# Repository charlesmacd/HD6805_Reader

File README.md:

# HD6805_Reader
(C) 2021 Charles MacDonald

WWW: http://techno-junk.org

Arduino shield used to read the internal ROM of some Hitachi HD6805 devices.

Based on the information and research of Sean Riddle (https://seanriddle.com/mc6805p2.html)

**NEW**: Check out the Dumping Log in the Wiki: https://github.com/charlesmacd/HD6805_Reader/wiki
 
## Overview

This project came about from the need to read the HD6805V1 MCU used in Sega's SP-400 printer.

## Files

```
/windows/hdread.exe
	Utilty to talk to Arduino via USB and retrieve HD6805 data
/utility 
	Utility source code
/firmware
	Arduino Uno firmware
/pcb/v1 
        Prototype shield
	Eagle schematics and layout for the first version of the shield. 
	Needs some wire links and a capacitor marked in yellow.
/pcb/v2
        Revised version of shield
	Eagle schematics and layout for the second version, fixes all the issues in v1
/pcb/gerbers
	Gerber files. These were set up using design rules for Elecrow/JLCPCB but 
	you definitely want to generate your own gerber	files for the fab you use.
/images
	Pictures of the shield
/datasheets
	Datasheets, patents, and other relevant material
```

## How to use

1. Insert the HD6805V1 device into the DIP socket with the pin 1 indicator facing toward the Arduino UNO's USB port.
2. Plug the Arduino Uno's USB cable into your PC.
3. Run the utility program: ```hdread read dump.bin```. It gives the following output

```
Status: Found port COM8.
Status: Attempting to open COM8.
Status: Waiting for Arduino to reboot.
Sending command.
Got command parameter = 06
Status: Test address wrapping.
Status: Seek first bus cycle.
Result: Found first bus cycle in 19 clocks.
Status: Seek first bus cycle.
Result: Found output sequence in 16 clocks.
Status: Seek zero bus cycle.
Result: Found address wrap in 4880 clocks.
Reading offset 0000
:
Reading offset 0F00
Checksum = 78
Status: Finished.
Normal exit.
Status: Normal exit.
Local checksum = 78
Status: Writing ROM image to file `dump.bin'.
Status: Writing decoded data to `dump.bin.log'.  
```

4. The ROM data is written to ```dump.bin```, and the raw data output for each NUM cycle is written to ```dump.bin.log```. The latter isn't necessary but can be useful for examining the reading sequence in more detail.

Note that while the entire 4K address space is dumped ROM data only corresponds to offsets 0x0080 to 0xFFF. The first 128 bytes are mapped to internal I/O, RAM, and unused areas and will not be consistent from dump to dump. The utility program blanks them out to 0xFF, but doesn't do that to the log file.

## Analyzing dumped data

You can run ```hdread check <file.bin>``` to analyze the self-check ROM data, if present. For a HD6805V1 it reports the following:

```
Self-check vectors:
* TIMER = $0FEA
* INT#  = $0FEC
* SWI   = $0FE7
* RES#  = $0F80
Customer vectors:
* TIMER = $0A46
* INT#  = $0A10
* SWI   = $07F0
* RES#  = $06E0
Self-check ROM analysis:
* Reset vector is valid.
* Internal checksum   = EA
* Calculated checksum = EA
* ROM SHA256 = 9088fee917e5a748c2f0b4f5458c1cbdabbd696291c69be6e605bae0ef779e8f
* ROM matches device type HD6805V1
```

The internal checksum is stored within the self-check ROM at address 0xFEF. It is computed by calculating the exclusive OR of all bytes from 0x080 to 0xFFF excluding 0xFEF and inverting the result. If the internal and calculated checksums don't match it's likely the ROM dump is bad and should be redumped.

The sha256sum covers addresses 0xF80 through 0xFE7. Two devices I dumped have identical programs, but it's possible other HD6805 variants have different
self-check programs. Please get in touch if you find a device with a different sha256sum.

## Board assembly and configuration

The original design had a TPS2041B to control power to the HD6805V1 in case there was any behavior worth examining that was tied to a power-up event, but in practice that isn't necessary. Thus components IC1, C1A, C1B, C2A, C2B, R8, R10, R24 and the yellow LED can be omitted.

### Board types

The V1 design was the first one I made and it works fine but needs some corrections:

* Wire links added from C0-C4 and NUM to Arduino inputs A0-A4 and A5.
* A 0.1uF capacitor across DIP socket pins 1,4.

The V2 design has these changes made and the schematic was cleaned up considerably so I'd advise building that one instead.
I haven't tested it myself but it was a minor set of changes.

### Bill of materials

| Location | Size | Type | Manufacturer P/N |
|- |- |- |- |
| C1A,C2A | 0603 | Ceramic, 0.1uF, 10V | C0603C104Z3VACTU |
 |C1B,C2B | 0603 | Ceramic, 0.01uF, 10V | 06035C103KAT2A |
| R1-R8/R11-R15/R16-R24 | 0603 | 1K ohm, 1/10W, any tolerance | CRCW06031K00FKEAC |
| R9/R10 | 0603 | 10K ohm, any tolerance | SFR03EZPF1002 |
| FLT | 3mm | Yellow LED, diffused | TLHY4400-AS12Z |
| IC1 | SOIC-8 | TPS2041B load switch | TPS2041BD |
| JP3/4/6/7 | N/A | Arduino UNO stacking headers | Adafruit P/N: 485 or Mouser P/N: 485-85 |

### Jumper configurations

See the photo for more details.

* For JP11 pins 2-3 should be shorted together so that the Arduino 5V is used for the HD6805V1 +5V input.

* For JP5 the jumper across all pins should be installed. Note on the V1 board the middle jumper (XTL) should be left open.

* For JP9-10 the jumpers should be arranged to specify 0x9D (from top to bottom is MSB to LSB, left=VCC, right=GND so jumper order is LRRLLLRL)

## Tested devices

1. ```Hitachi HD6805V1P A08```
   Dump seems good. Internal checksum is 0xEA.

2. ```Termbray 117-017 HD6805V1B65P 8A3```
   Dump seems good. Internal checksum is 0x8A. Same self-check ROM content as above.

3. ```Hitachi HD6805V1A81P 800-5 A24```

   Dump seems good. This is a variant where the self-check ROM is not present and instead contains more customer ROM code and data.
   Thus the self-check mode is not supported and only the user vector table is present.

Note that all the chips run a somewhat hot normally.
The Arduino Uno I tested with draws about 40mA idle, and with a HD6805V1 installed it draws 120mA when the clock is static.
But use caution when testing the PCB after assembly and check all voltages **before** inserting a chip and attempting to read it.

## Technical overview

The HD6805V1 is a variant of the Motorola MC6805 designed by Hitachi. Check out the datasheet for more information.

### Memory map
```
0000-0009 : Internal registers (I/O, timer)
000A-001F : Unused
0020-007F : Work RAM (96 bytes)
0080-0F7F : Customer ROM (3848 bytes)
0F80-0FEF : Self-check ROM (120 bytes)
0FF0-0FF7 : Self-check ROM vector table
```

## Operating modes
* Normal
  * Customer ROM is used
* Self-check
  * Self-test ROM is used
  * Enable by pulling TIMER pin to +9V 
* Non-user mode
  * External ROM is used
  * Enable by pulling NUM pin to +5V

## Non-user mode

In non-user mode the I/O ports are repurposed to present an external memory bus similar to the MC146805E2:

* Port A is the external data bus where opcodes are input.
* Port B is multiplexed between part of the address bus and the internal data bus.
* Port C outputs several address lines on PC[4,2:0] and a control signal, possibly R/W# on PC3.

This arrangement would allow the HD6805V1 to execute program code from an external EPROM. A slight difference between it and the MC146805E2 is how the address bus is arranged:

* PB[7:0] => {A9, A8, A5, A5, A6, A1, A7, A0}
* PC[4,2:0] => {A11, A3, A2, A10}

What's missing is a signal used to demultiplex port B. Hitachi's US patent 5,179,694 describes a function for the HD6301V microcontroller where the E clock (a synchronization signal that runs at 1/4th of the oscillator clock) isn't normally accessible but can be output in some conditions. It follows with a brief note that the HD6805 NUM pin performs a similar function when it is pulled high, outputting the sync signal for device testing purposes.

Tests on the HD6805V1 confirms this; in non-user mode the NUM pin will output a clock signal at 1/4th of the rate presented on the EXTAL pin. Conceptually this seems to map closest to the MC146805E2's DS signal. This can be used to demultiplex port B.

## Device configuration in NUM mode for dumping internal ROM

For dumping ROM data I configured the pins as follows on the Arduino shield:

* RES# : Pulled high via 1K ohm resistor, can be driven low to reset the device and restart the output stream of data.
* INT# : Pulled high via 1K ohm resistor, unused
* EXTAL : Driven by Arduino to clock the HD6805V1
* XTAL : I've left it floating with good results, but it should probably be grounded.
* NUM : Pulled high via 1K ohm resistor, in NUM mode it becomes a sync output used to demultiplex port B
* TIMER : Pulled high via 1K ohm resistor
* PB[7:0],PC[2:0],NUM : Input to Arduino for logging
* PA[7:0] : Connected to eight jumpers to specify an opcode (in this case 0x9D for NOP)
* PD[7:0] : Unused, pulled high via 1K ohm resistor network. The pull-ups may not be necessary.
* PC[7:3] : Unused

## Exploiting non-user mode

The most useful side effect of non-user mode is that the internal data bus multiplexed on port B outputs whatever internal memory location the program counter is currently addressing, allowing the entirety of the HD6805V1 address space to be read out. To control this process to dump ROM data a simple 1-byte instruction like NOP or RSP can have their opcode driven on to port A and the HD6805 will continuously execute it, output data from the current internal address, and increment the program counter by one. This process can continue indefinitely until all ROM data has been read.

## Reset timing

* Clock cycle 1 : NUM low, port B,C output address 0xFFE.
* Clock cycle 2 : NUM high, port B outputs data from internal ROM address 0xFFE. This is the reset vector LSB.
* Clock cycle 3 : NUM low, port B,C output address 0xFFF.
* Clock cycle 4 : NUM high, port B outputs data from internal ROM address 0xFFF. This is the reset vector MSB.
* Clock cycle 5 : NUM low, port B,C output address 0x000.
* Clock cycle 6 : NUM high, port B outputs 0xFF.
* Clock cycle 7 : NUM low, port B,C output address 0xD9D.
* Clock cycle 8 : NUM high, port B outputs data from internal ROM address 0xD9D.

Before this sequence starts there can be 18 to 20 clocks needed for the HD6805V1 to come out of the reset state.

Since we're gating NOP (0x9D) on to port A, the reset vector read is 0xD9D.

## NOP execution timing

* Clock cycle 1 : NUM low, Port B outputs address.
* Clock cycle 2 : NUM high, port B outputs internal data bus.
* Clock cycle 3 : NUM low, Port B outputs address.
* Clock cycle 4 : NUM high, port B outputs internal data bus. At the next clock edge the program counter increments.

As long as NOP or a similar type of opcode is presented this sequence repeats indefinitely.

Here cycles 3,4 present the same data and address as cycles 1,2. When reading ROM the data will be consistent, but when reading first 128 bytes assigned to
I/O, RAM, and unused locations the data can differ.

## Dumping ROM data

As the Arduino shield always outputs 0x9D on to port D, the reset vector is 0xD9D and internal data starts getting fetched from that address.
A more complex device might want to dynamically drive port A to define a reset vector like 0x000 or 0x080, it's simple enough to clock the device 
until the address bus increments from 0xD9D to 0xFFF and then wraps to 0x000. At this point the entire 4K internal address space can be read out.

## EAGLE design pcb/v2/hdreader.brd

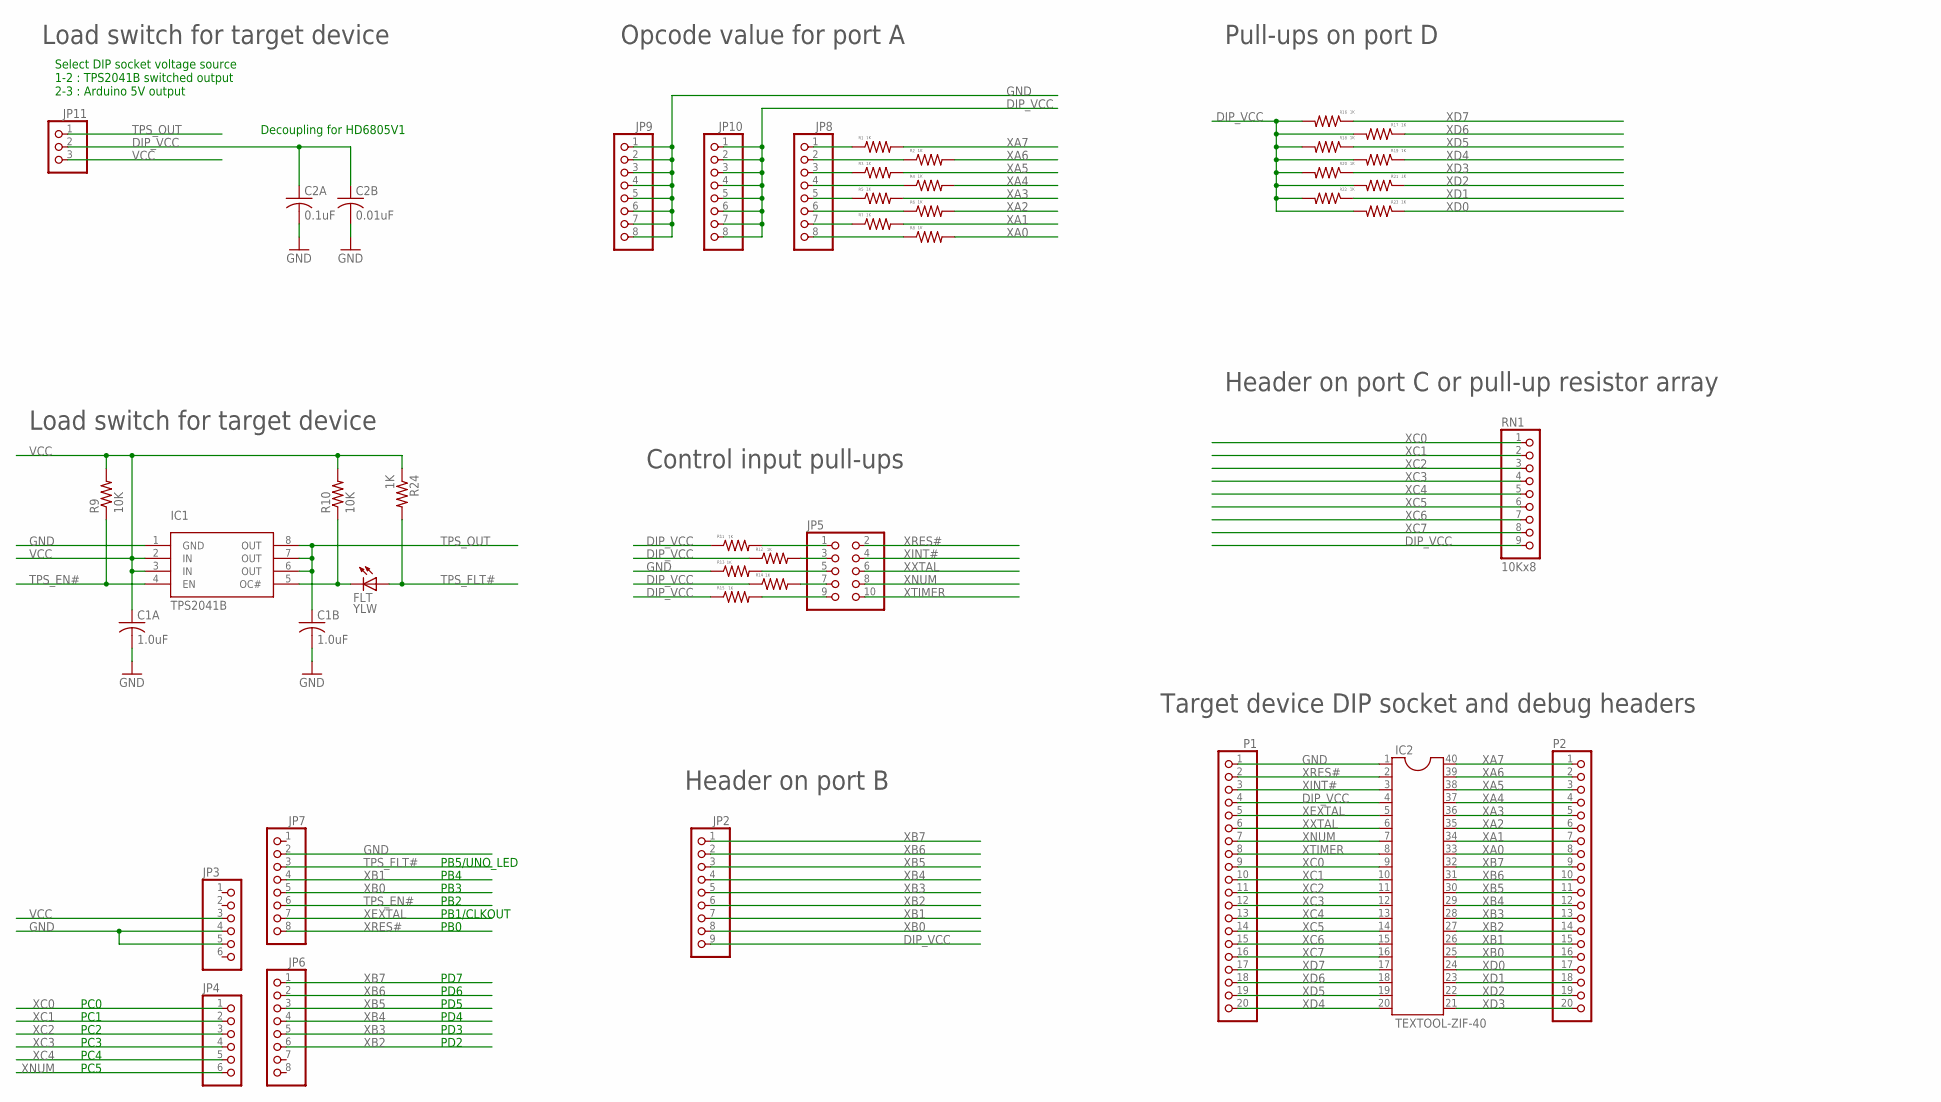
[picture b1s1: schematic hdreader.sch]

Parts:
C1A, C1B: 1.0uF; C0603
C2A: 0.1uF; C0603
C2B: 0.01uF; C0603
FLT: YLW; LED5MM
IC1: TPS2041B; SOIC8
IC2: TEXTOOL-ZIF-40; TEXTOOL-DIP-40
JP2: PINHD-1X9; 1X09
JP3, JP4: PINHD-1X6; 1X06
JP5: PINHD-2X5; 2X05
JP6, JP7, JP8, JP9, JP10: PINHD-1X8; 1X08
JP11: PINHD-1X3; 1X03
P1, P2: PINHD-1X20; 1X20
R1, R2, R3, R4, R5, R6, R7, R8, R11, R12, R13, R14, R15, R16, R17, R18, R19, R20, R21, R22, R23, R24: 1K; R0603
R9, R10: 10K; R0603
RN1: 10Kx8; 1X09

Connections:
DIP_VCC: C2A.1, C2B.1, IC2.4, JP2.9, JP10.1, JP10.2, JP10.3, JP10.4, JP10.5, JP10.6, JP10.7, JP10.8, JP11.2, P1.4, R11.1, R12.1, R14.1, R15.1, R16.2, R17.2, R18.2, R19.2, R20.2, R21.2, R22.2, R23.2, RN1.9
GND: C1A.2, C1B.2, C2A.2, C2B.2, IC1.1 (GND), IC2.1, JP3.4, JP3.5, JP7.2, JP9.1, JP9.2, JP9.3, JP9.4, JP9.5, JP9.6, JP9.7, JP9.8, P1.1, R13.1
unnamed: FLT.A, R24.2
unnamed: JP5.1, R11.2
unnamed: JP5.3, R12.2
unnamed: JP5.5, R13.2
unnamed: JP5.7, R14.2
unnamed: JP5.9, R15.2
TPS_EN#: IC1.4 (EN), JP7.6, R9.1
TPS_FLT#: FLT.K (C), IC1.5 (OC#), JP7.3, R10.1
TPS_OUT: C1B.1, IC1.6 (OUT), IC1.7 (OUT), IC1.8 (OUT), JP11.1
VCC: C1A.1, IC1.2 (IN), IC1.3 (IN), JP3.3, JP11.3, R9.2, R10.2, R24.1
XA0: IC2.33, P2.8, R8.2
XA1: IC2.34, P2.7, R7.2
XA2: IC2.35, P2.6, R6.2
XA3: IC2.36, P2.5, R5.2
XA4: IC2.37, P2.4, R4.2
XA5: IC2.38, P2.3, R3.2
XA6: IC2.39, P2.2, R2.2
XA7: IC2.40, P2.1, R1.2
XAP0: JP8.8, R8.1
XAP1: JP8.7, R7.1
XAP2: JP8.6, R6.1
XAP3: JP8.5, R5.1
XAP4: JP8.4, R4.1
XAP5: JP8.3, R3.1
XAP6: JP8.2, R2.1
XAP7: JP8.1, R1.1
XB0: IC2.25, JP2.8, JP7.5, P2.16
XB1: IC2.26, JP2.7, JP7.4, P2.15
XB2: IC2.27, JP2.6, JP6.6, P2.14
XB3: IC2.28, JP2.5, JP6.5, P2.13
XB4: IC2.29, JP2.4, JP6.4, P2.12
XB5: IC2.30, JP2.3, JP6.3, P2.11
XB6: IC2.31, JP2.2, JP6.2, P2.10
XB7: IC2.32, JP2.1, JP6.1, P2.9
XC0: IC2.9, JP4.1, P1.9, RN1.1
XC1: IC2.10, JP4.2, P1.10, RN1.2
XC2: IC2.11, JP4.3, P1.11, RN1.3
XC3: IC2.12, JP4.4, P1.12, RN1.4
XC4: IC2.13, JP4.5, P1.13, RN1.5
XC5: IC2.14, P1.14, RN1.6
XC6: IC2.15, P1.15, RN1.7
XC7: IC2.16, P1.16, RN1.8
XD0: IC2.24, P2.17, R23.1
XD1: IC2.23, P2.18, R22.1
XD2: IC2.22, P2.19, R21.1
XD3: IC2.21, P2.20, R20.1
XD4: IC2.20, P1.20, R19.1
XD5: IC2.19, P1.19, R18.1
XD6: IC2.18, P1.18, R17.1
XD7: IC2.17, P1.17, R16.1
XEXTAL: IC2.5, JP7.7, P1.5
XINT#: IC2.3, JP5.4, P1.3
XNUM: IC2.7, JP4.6, JP5.8, P1.7
XRES#: IC2.2, JP5.2, JP7.8, P1.2
XTIMER: IC2.8, JP5.10, P1.8
XXTAL: IC2.6, JP5.6, P1.6

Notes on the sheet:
PB0
PB1/CLKOUT
PB2
PB3
PB4
PB5/UNO_LED
PD2
PD3
PD4
PD5
PD6
PD7
Select DIP socket voltage source 1-2 : TPS2041B switched output 2-3 : Arduino 5V output
Decoupling for HD6805V1
PC0
PC1
PC2
PC3
PC4
PC5
Load switch for target device
Opcode value for port A
Control input pull-ups
Header on port C or pull-up resistor array
Header on port B
Target device DIP socket and debug headers
Pull-ups on port D

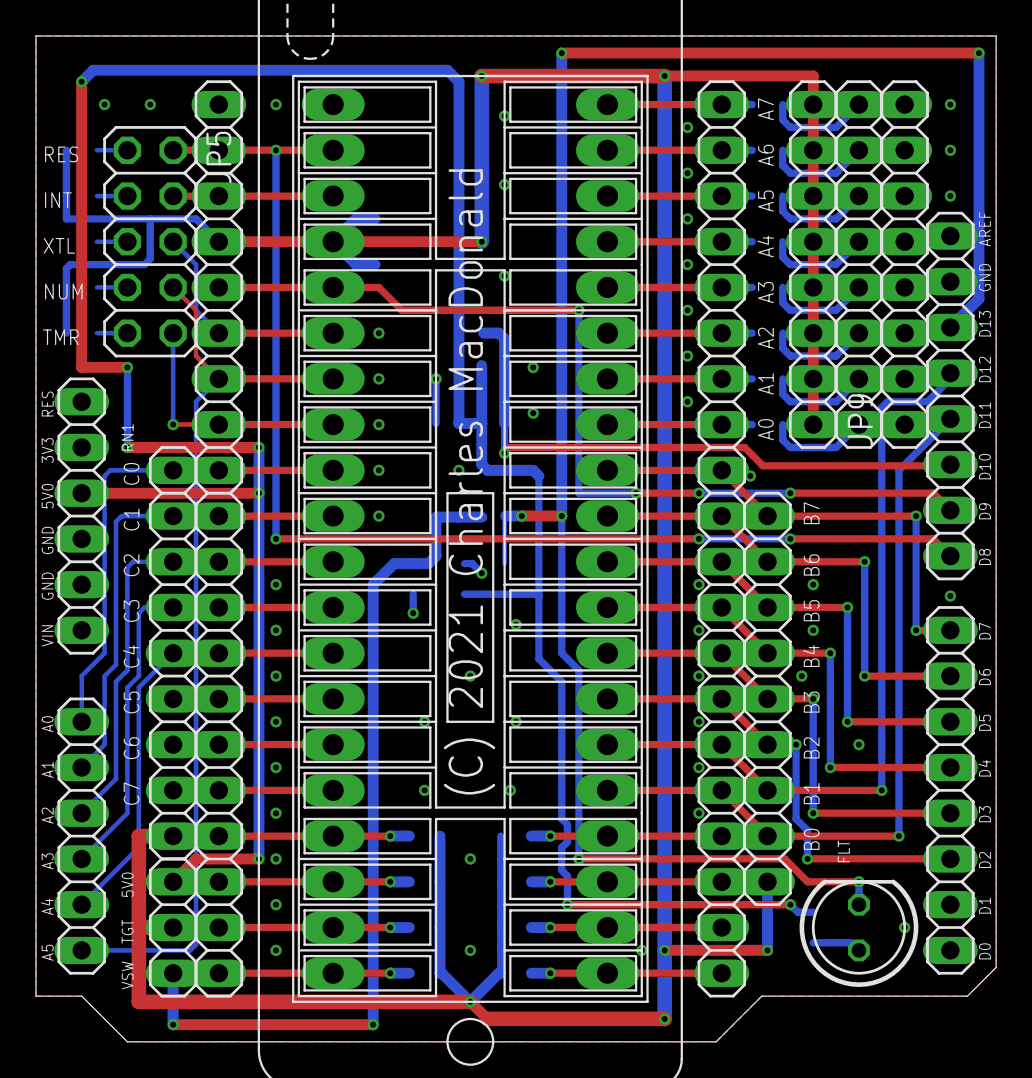
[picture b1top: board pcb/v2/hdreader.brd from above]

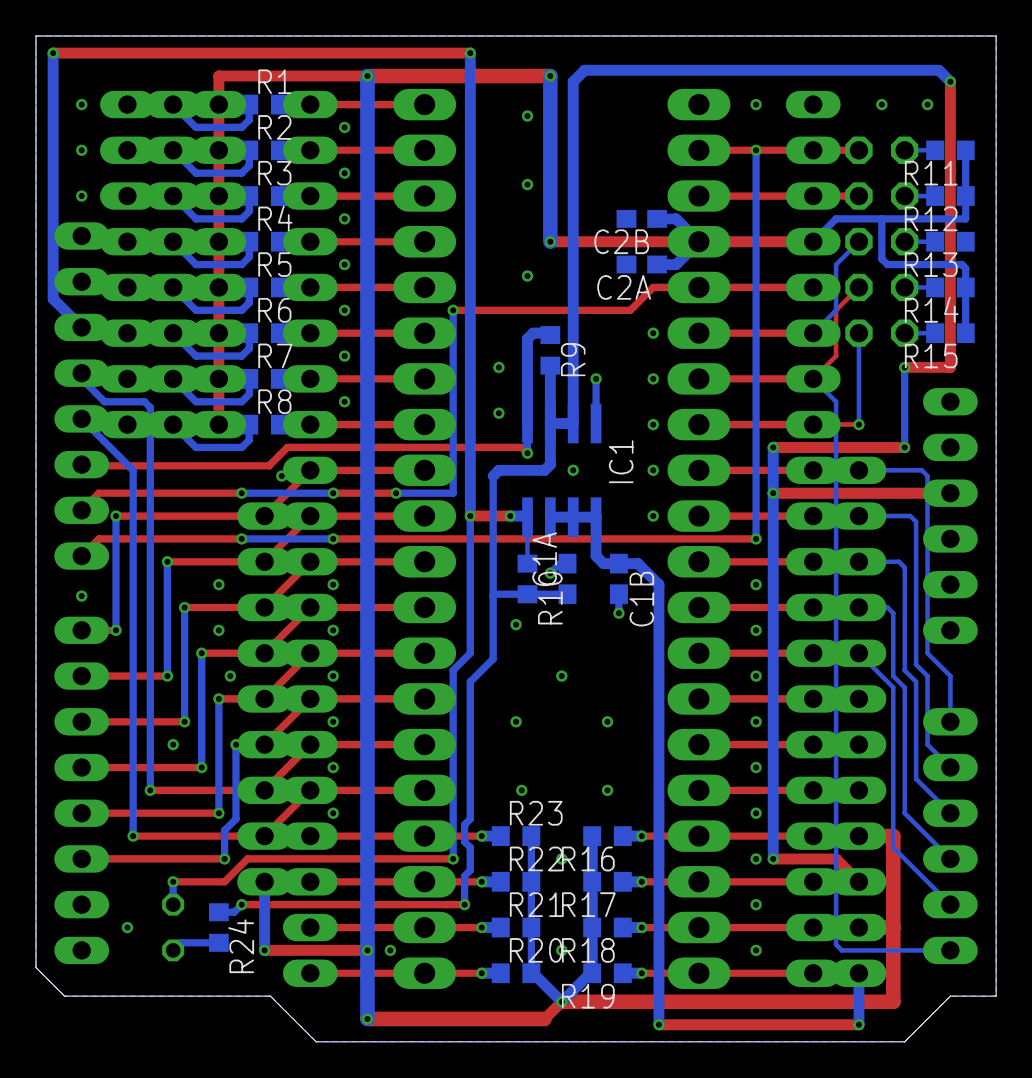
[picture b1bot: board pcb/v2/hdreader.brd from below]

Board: 2 copper layers, 53.3 x 55.9 mm, 44 parts (29 on the bottom side), 58 nets.

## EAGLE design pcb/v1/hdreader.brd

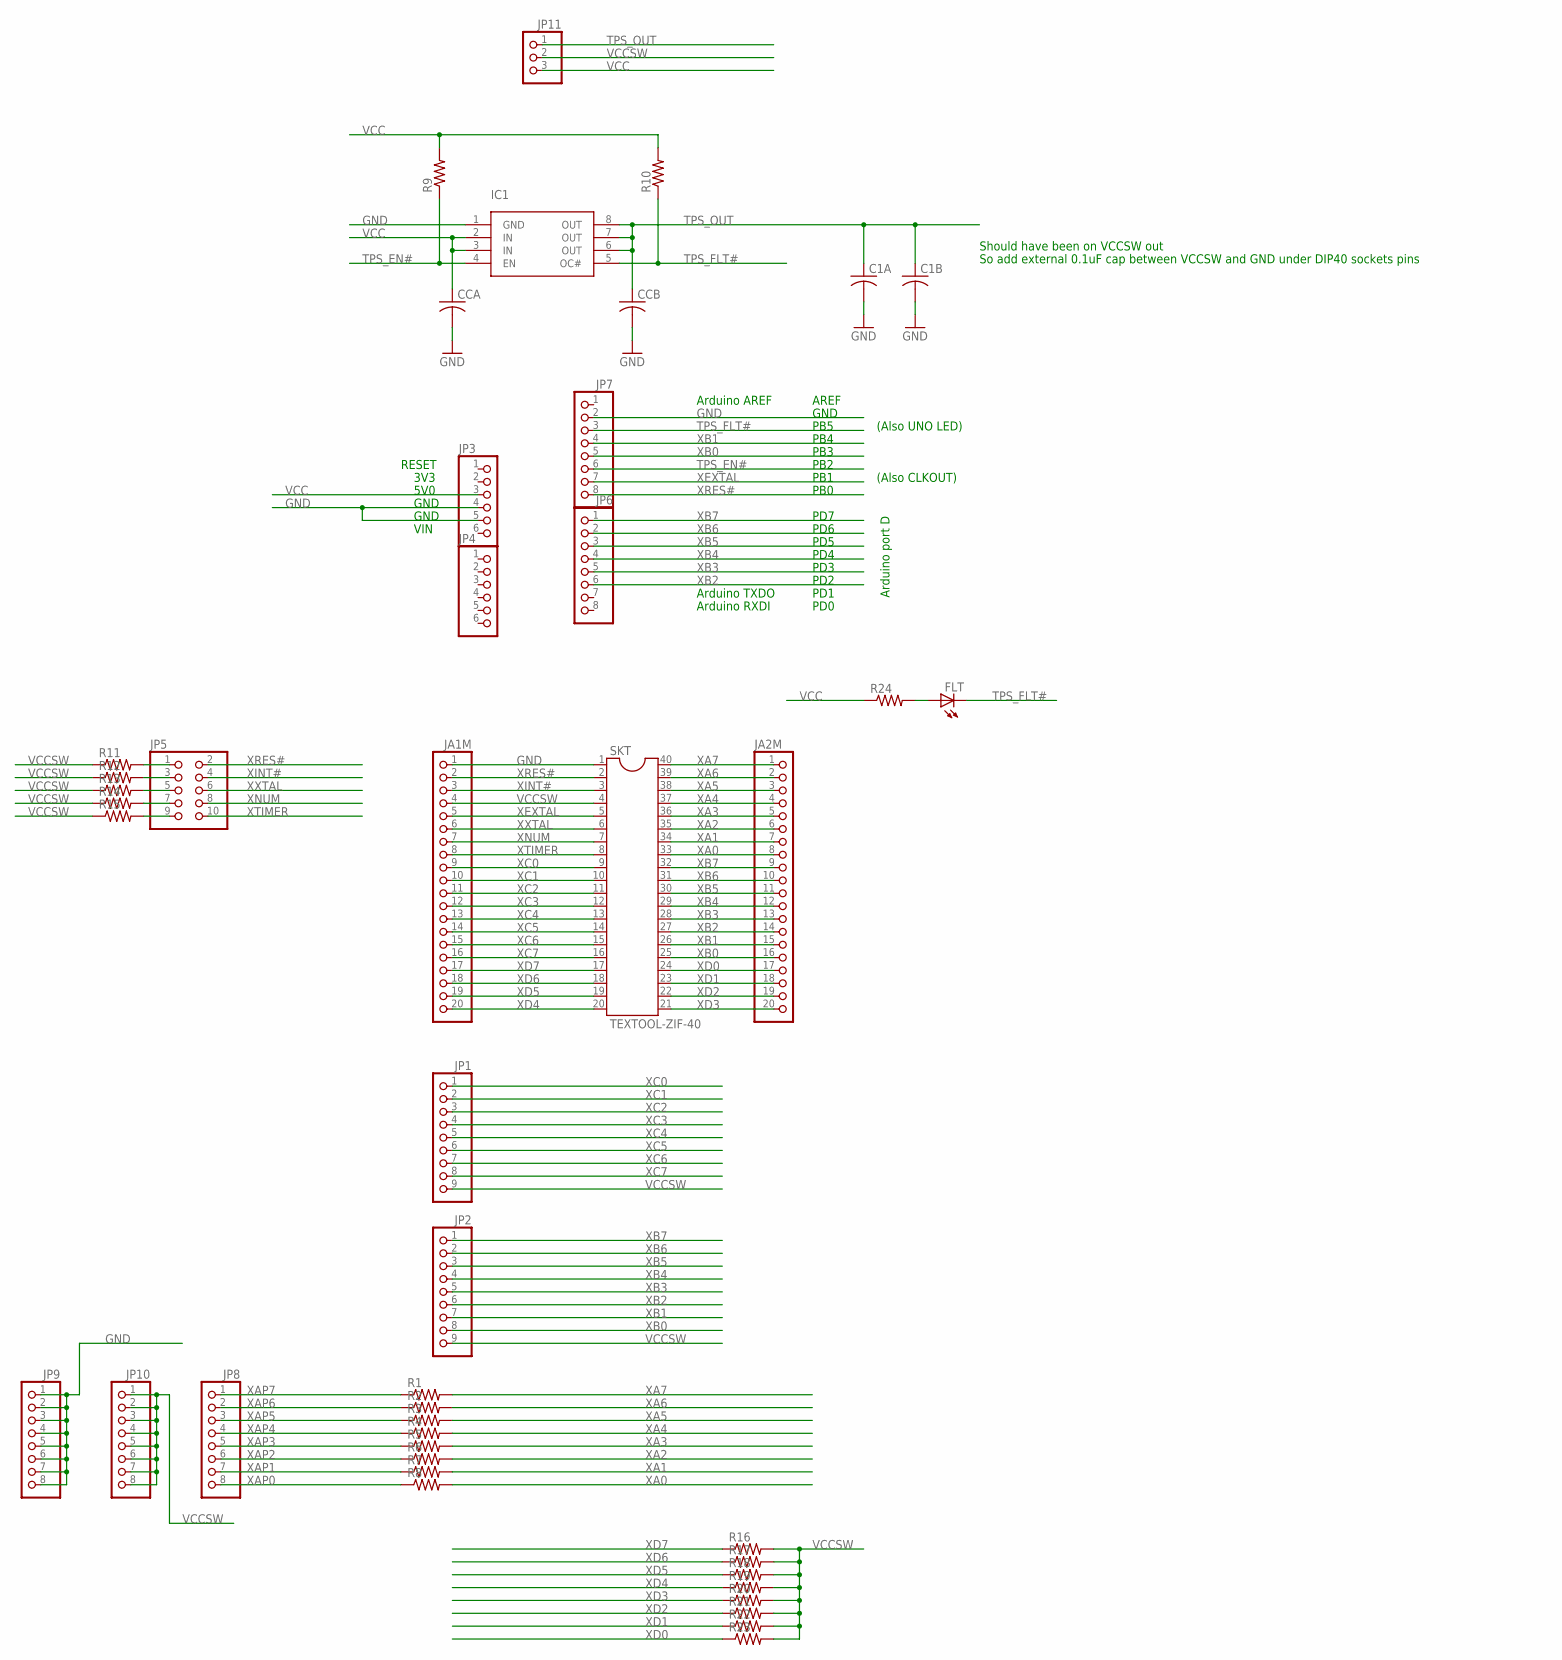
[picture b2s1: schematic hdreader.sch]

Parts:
C1A, C1B: C-USC0603; C0603
CCA: C-USC0603; C0603
CCB: C-USC0603; C0603
FLT: LED3MM
IC1: TPS2051D; SOIC8
JA1M, JA2M: PINHD-1X20; 1X20
JP1, JP2: PINHD-1X9; 1X09
JP3, JP4: PINHD-1X6; 1X06
JP5: PINHD-2X5; 2X05
JP6, JP7, JP8, JP9, JP10: PINHD-1X8; 1X08
JP11: PINHD-1X3; 1X03
R1, R2, R3, R4, R5, R6, R7, R8, R9, R10, R11, R12, R13, R14, R15, R16, R17, R18, R19, R20, R21, R22, R23, R24: R-US_R0603; R0603
SKT: TEXTOOL-ZIF-40; TEXTOOL-DIP-40

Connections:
GND: C1A.2, C1B.2, CCA.2, CCB.2, IC1.1 (GND), JA1M.1, JP3.4, JP3.5, JP7.2, JP9.1, JP9.2, JP9.3, JP9.4, JP9.5, JP9.6, JP9.7, JP9.8, SKT.1
unnamed: FLT.A, R24.2
unnamed: JP5.1, R11.2
unnamed: JP5.3, R12.2
unnamed: JP5.5, R13.2
unnamed: JP5.7, R14.2
unnamed: JP5.9, R15.2
TPS_EN#: IC1.4 (EN), JP7.6, R9.1
TPS_FLT#: FLT.K (C), IC1.5 (OC#), JP7.3, R10.1
TPS_OUT: C1A.1, C1B.1, CCB.1, IC1.6 (OUT), IC1.7 (OUT), IC1.8 (OUT), JP11.1
VCC: CCA.1, IC1.2 (IN), IC1.3 (IN), JP3.3, JP11.3, R9.2, R10.2, R24.1
VCCSW: JA1M.4, JP1.9, JP2.9, JP10.1, JP10.2, JP10.3, JP10.4, JP10.5, JP10.6, JP10.7, JP10.8, JP11.2, R11.1, R12.1, R13.1, R14.1, R15.1, R16.2, R17.2, R18.2, R19.2, R20.2, R21.2, R22.2, R23.2, SKT.4
XA0: JA2M.8, R8.2, SKT.33
XA1: JA2M.7, R7.2, SKT.34
XA2: JA2M.6, R6.2, SKT.35
XA3: JA2M.5, R5.2, SKT.36
XA4: JA2M.4, R4.2, SKT.37
XA5: JA2M.3, R3.2, SKT.38
XA6: JA2M.2, R2.2, SKT.39
XA7: JA2M.1, R1.2, SKT.40
XAP0: JP8.8, R8.1
XAP1: JP8.7, R7.1
XAP2: JP8.6, R6.1
XAP3: JP8.5, R5.1
XAP4: JP8.4, R4.1
XAP5: JP8.3, R3.1
XAP6: JP8.2, R2.1
XAP7: JP8.1, R1.1
XB0: JA2M.16, JP2.8, JP7.5, SKT.25
XB1: JA2M.15, JP2.7, JP7.4, SKT.26
XB2: JA2M.14, JP2.6, JP6.6, SKT.27
XB3: JA2M.13, JP2.5, JP6.5, SKT.28
XB4: JA2M.12, JP2.4, JP6.4, SKT.29
XB5: JA2M.11, JP2.3, JP6.3, SKT.30
XB6: JA2M.10, JP2.2, JP6.2, SKT.31
XB7: JA2M.9, JP2.1, JP6.1, SKT.32
XC0: JA1M.9, JP1.1, SKT.9
XC1: JA1M.10, JP1.2, SKT.10
XC2: JA1M.11, JP1.3, SKT.11
XC3: JA1M.12, JP1.4, SKT.12
XC4: JA1M.13, JP1.5, SKT.13
XC5: JA1M.14, JP1.6, SKT.14
XC6: JA1M.15, JP1.7, SKT.15
XC7: JA1M.16, JP1.8, SKT.16
XD0: JA2M.17, R23.1, SKT.24
XD1: JA2M.18, R22.1, SKT.23
XD2: JA2M.19, R21.1, SKT.22
XD3: JA2M.20, R20.1, SKT.21
XD4: JA1M.20, R19.1, SKT.20
XD5: JA1M.19, R18.1, SKT.19
XD6: JA1M.18, R17.1, SKT.18
XD7: JA1M.17, R16.1, SKT.17
XEXTAL: JA1M.5, JP7.7, SKT.5
XINT#: JA1M.3, JP5.4, SKT.3
XNUM: JA1M.7, JP5.8, SKT.7
XRES#: JA1M.2, JP5.2, JP7.8, SKT.2
XTIMER: JA1M.8, JP5.10, SKT.8
XXTAL: JA1M.6, JP5.6, SKT.6

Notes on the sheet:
Arduino port D
PB0
PB1
PB2
PB3
PB4
PB5
(Also UNO LED)
(Also CLKOUT)
PD0
PD1
PD2
PD3
PD4
PD5
PD6
PD7
Arduino TXDO
Arduino RXDI
Arduino AREF
GND
AREF
VIN
5V0
3V3
RESET
Should have been on VCCSW out
So add external 0.1uF cap between VCCSW and GND under DIP40 sockets pins

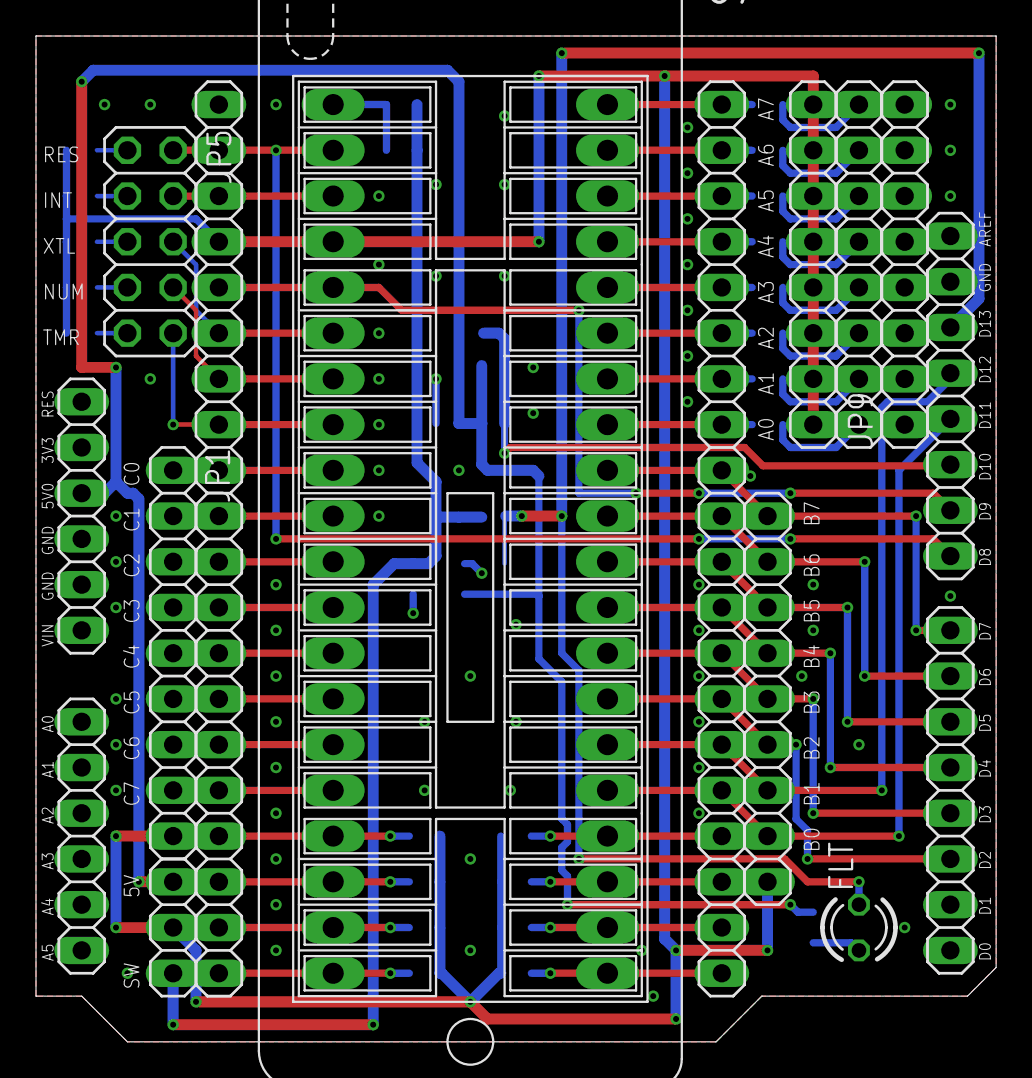
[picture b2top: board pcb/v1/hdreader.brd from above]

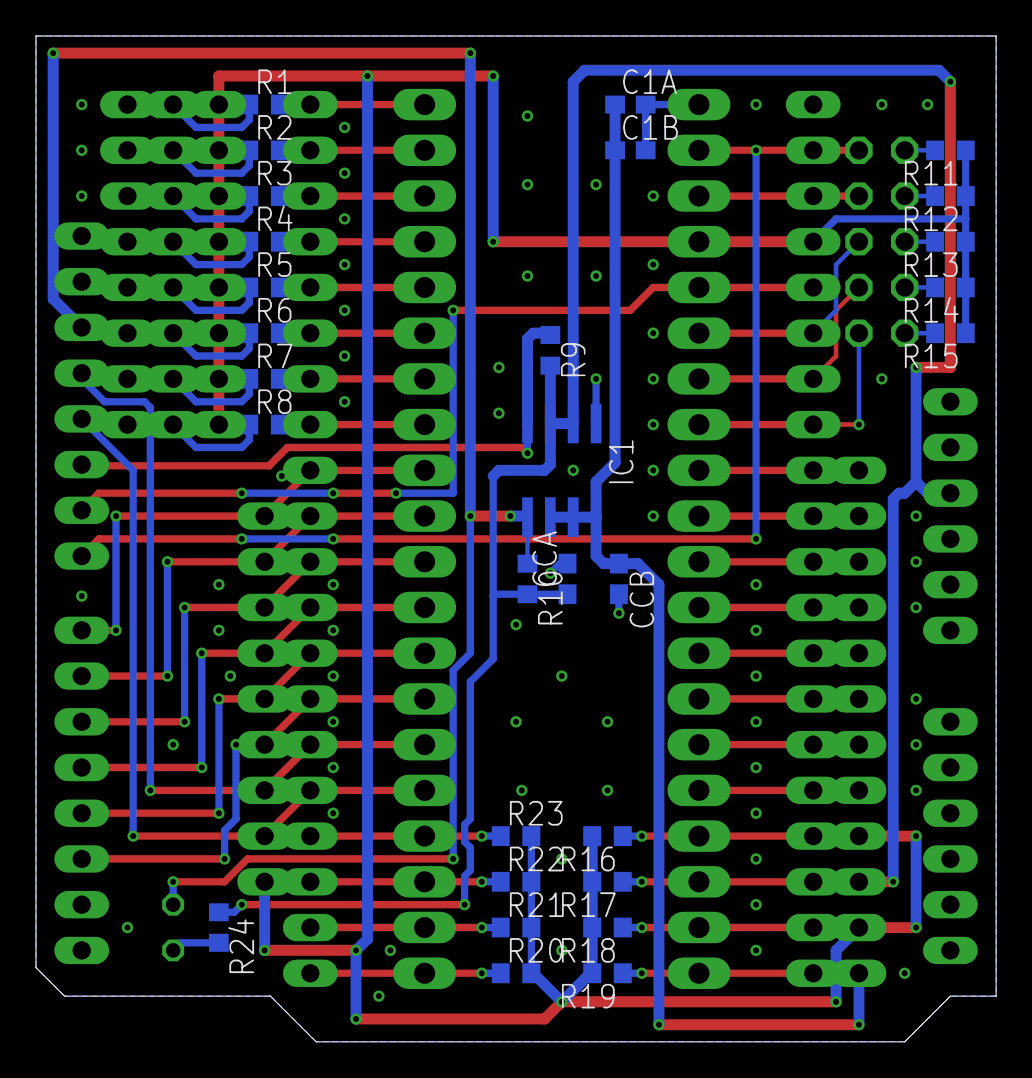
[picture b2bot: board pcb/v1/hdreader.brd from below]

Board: 2 copper layers, 53.3 x 55.9 mm, 44 parts (29 on the bottom side), 58 nets.

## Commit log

2021-12-06 Update README.md
    Fixed jumper description
2021-12-06 Update README.md
    Fixed PC3/4 description
2021-12-06 Update README.md
    Fixed typos
2021-12-07 Update README.md
    Added notes about internal checksums and confirmed the dump status of the third chip.
2021-12-12 Added ROM check feature
2021-12-12 Update README.md
    Updated documentation to cover ROM analysis/checking.
2021-12-19 Update README.md
    Added bill of materials
2021-12-19 Add files via upload
    Bottom side of assembled V1 board.
2021-12-26 Fixed typos in descriptions
